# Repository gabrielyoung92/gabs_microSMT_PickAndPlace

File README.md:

# MicroSMT PNPv3 machine and feeders

Code, CAD, board files and operating notes for this machine. The hardware designs
and original firmware are by [MicroSMT](https://github.com/microsmt).
[Credits](CREDITS.md) · [Licences](THIRD_PARTY_NOTICES.md).

## Machine software

The Dell OptiPlex runs Debian 13 and OpenPnP. OpenPnP connects directly to the
Smoothieboard and cameras, and handles motion, pickup teaching, nozzles and jobs.
The feeder host owns the separate USB–RS485 adapter and serves the dashboard at
`http://machine-hostname/`, plain HTTP port 80 without login. OpenPnP advances
feeders through TCP `127.0.0.1:5001`.

| Software | Source and instructions |
| --- | --- |
| Dashboard, feeder host and OpenPnP companion | [USB_host/](Bing-feeder/V485-feeder/USB_host/README.md) |
| Universal feeder firmware **0.1.4**, bootloader and serial tools | [CODE_feeder/](Bing-feeder/V485-feeder/CODE_feeder/README.md) |
| Machine configuration and calibration | [Machine notes](Microsmt-PNPv3/docs/README.md) |
| EEPROM layout, saved settings and text/quantity limits | [EEPROM.md](EEPROM.md) |
| Remaining work | [TODO.md](TODO.md) |

The dashboard covers feeder state/errors, reel stock, motor/switch settings,
input tests and firmware updates. It also edits OpenPnP parts/packages and checks
remaining job stock. Tip compatibility is selected through packages; physical
nozzle setup stays in OpenPnP.

Build the feeder application with `pio run -e v485` from `CODE_feeder`.
It creates the dashboard firmware bundle automatically. Deploy the bundle and
select **Update** or **Update all outdated**, using the installed bootloader.
See the guides above for installation and operating details.

## Parts and boards

<p>

</p>

| Collection | Contents |
| --- | --- |
| [V485 feeders](Bing-feeder/V485-feeder/README.md) | 8/12/16/24 mm parts, PCBs and firmware |
| [V485 controller](Bing-feeder/V485-Feeder%20Controller/README.md) | ESP32-C3 controller and RS485 busbars |
| [V3 feeders](Bing-feeder/V3-feeder/README.md) | Parts, PCBs, source and assembly references |
| [V3 controller](Bing-feeder/V3-Feeder%20Controller/README.md) | Mega2560 sketch, controller PCB and busbars |
| [PNPv3 machine](Microsmt-PNPv3/README.md) | Frame parts, nozzle rack, strip feeders, motherboard and manuals |
| [KiCad projects](tools/kicad/README.md) | Editable board references, source comparisons and rebuild tools |
| [Missing V485 parts](V485-MISSING-PARTS.md) | Missing files and questions for the vendor |
| [STM32 source builds](Bing-feeder/STM32-BUILD.txt) | V485 build and V3 project requirements |

STL files are for printing; STEP files are for editing. Board folders contain
Gerbers, `KiCad/`, `docs/` and `photos/`. Keep each KiCad folder together for its
local libraries. Read the [recovery notes](tools/kicad/RECOVERY_NOTES.md) before
changing recovered copper or ordering boards.

View galleries on GitHub or with **Ctrl+Shift+V** in VS Code. Keep the photos
beside their READMEs. Machine profiles, stock databases, credentials and generated
builds remain outside Git. Local changes were prepared with ChatGPT assistance;
upstream attribution and licence notices remain in the repository.

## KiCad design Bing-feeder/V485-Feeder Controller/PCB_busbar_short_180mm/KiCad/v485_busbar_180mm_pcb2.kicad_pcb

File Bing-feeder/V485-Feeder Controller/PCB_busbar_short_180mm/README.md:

# V485 busbars — 180 mm

> Designs and original files by [MicroSMT](https://github.com/microsmt/Bing-feeder). [Credits and local changes](../../../CREDITS.md).

[Back to collection](../README.md)

Gerbers, editable KiCad files and previews are below.

## KiCad files

Open `.kicad_pro` in **KiCad 10**. Keep the whole `KiCad/` folder together; it contains the local libraries.

The schematics show pad numbers and connections. Use the supplied schematic for pin functions. Review the reported ERC/DRC findings before making a board.

| Project | Open in KiCad | Supporting reports |
| --- | --- | --- |
| V485 short busbar PCB1 | [v485_busbar_180mm_pcb1.kicad_pro](KiCad/v485_busbar_180mm_pcb1.kicad_pro) | [Recovery](docs/v485_busbar_180mm_pcb1-recovery.json) · [Validation](docs/v485_busbar_180mm_pcb1-validation.json) |
| V485 short busbar PCB2 | [v485_busbar_180mm_pcb2.kicad_pro](KiCad/v485_busbar_180mm_pcb2.kicad_pro) | [Recovery](docs/v485_busbar_180mm_pcb2-recovery.json) · [Validation](docs/v485_busbar_180mm_pcb2-validation.json) |
| V485 short busbar PCB4 | [v485_busbar_180mm_pcb4.kicad_pro](KiCad/v485_busbar_180mm_pcb4.kicad_pro) | [Recovery](docs/v485_busbar_180mm_pcb4-recovery.json) · [Validation](docs/v485_busbar_180mm_pcb4-validation.json) |

[Recovery details](docs/KICAD_RECOVERY.md) · [Method and editing limits](../../../tools/kicad/RECOVERY_NOTES.md)

## PCB1 Gerber views

[Download Gerber ZIP](Gerber_PCB1_2026-10-09.zip)

<table>
<tr>
<td align="center"><br><sub>Top</sub></td>
<td align="center"><br><sub>Bottom</sub></td>
<td align="center"><br><sub>Top-side isometric</sub></td>
</tr>
</table>

## PCB2 Gerber views

[Download Gerber ZIP](Gerber_PCB2_2026-10-09.zip)

<table>
<tr>
<td align="center"><br><sub>Top</sub></td>
<td align="center"><br><sub>Bottom</sub></td>
<td align="center"><br><sub>Top-side isometric</sub></td>
</tr>
</table>

## PCB4 Gerber views

[Download Gerber ZIP](Gerber_PCB4_2026-10-09.zip)

<table>
<tr>
<td align="center"><br><sub>Top</sub></td>
<td align="center"><br><sub>Bottom</sub></td>
<td align="center"><br><sub>Top-side isometric</sub></td>
</tr>
</table>

## Assembly notes

MicroSMT supplies 180 mm PCB busbars because the shorter sections are easier to transport. **PCB1, PCB2 and PCB4 each require two pieces.**

Gerber previews use display colours and an assumed 1.6 mm thickness; use source data for manufacturing dimensions.

## KiCad previews

KiCad reconstruction views; source Gerber views are above.

### V485 short busbar PCB1

<table>
<tr>
<td align="center"><br><sub>Recovered schematic</sub></td>
<td align="center"><br><sub>Recovered PCB top</sub></td>
<td align="center"><br><sub>Recovered PCB bottom</sub></td>
</tr>
</table>

[Sheet overview](photos/kicad-v485_busbar_180mm_pcb1-overview.jpg) · [Components 1](photos/kicad-v485_busbar_180mm_pcb1-sheet-01.jpg)

### V485 short busbar PCB2

<table>
<tr>
<td align="center"><br><sub>Recovered schematic</sub></td>
<td align="center"><br><sub>Recovered PCB top</sub></td>
<td align="center"><br><sub>Recovered PCB bottom</sub></td>
</tr>
</table>

[Sheet overview](photos/kicad-v485_busbar_180mm_pcb2-overview.jpg) · [Components 1](photos/kicad-v485_busbar_180mm_pcb2-sheet-01.jpg)

### V485 short busbar PCB4

<table>
<tr>
<td align="center"><br><sub>Recovered schematic</sub></td>
<td align="center"><br><sub>Recovered PCB top</sub></td>
<td align="center"><br><sub>Recovered PCB bottom</sub></td>
</tr>
</table>

[Sheet overview](photos/kicad-v485_busbar_180mm_pcb4-overview.jpg) · [Components 1](photos/kicad-v485_busbar_180mm_pcb4-sheet-01.jpg)

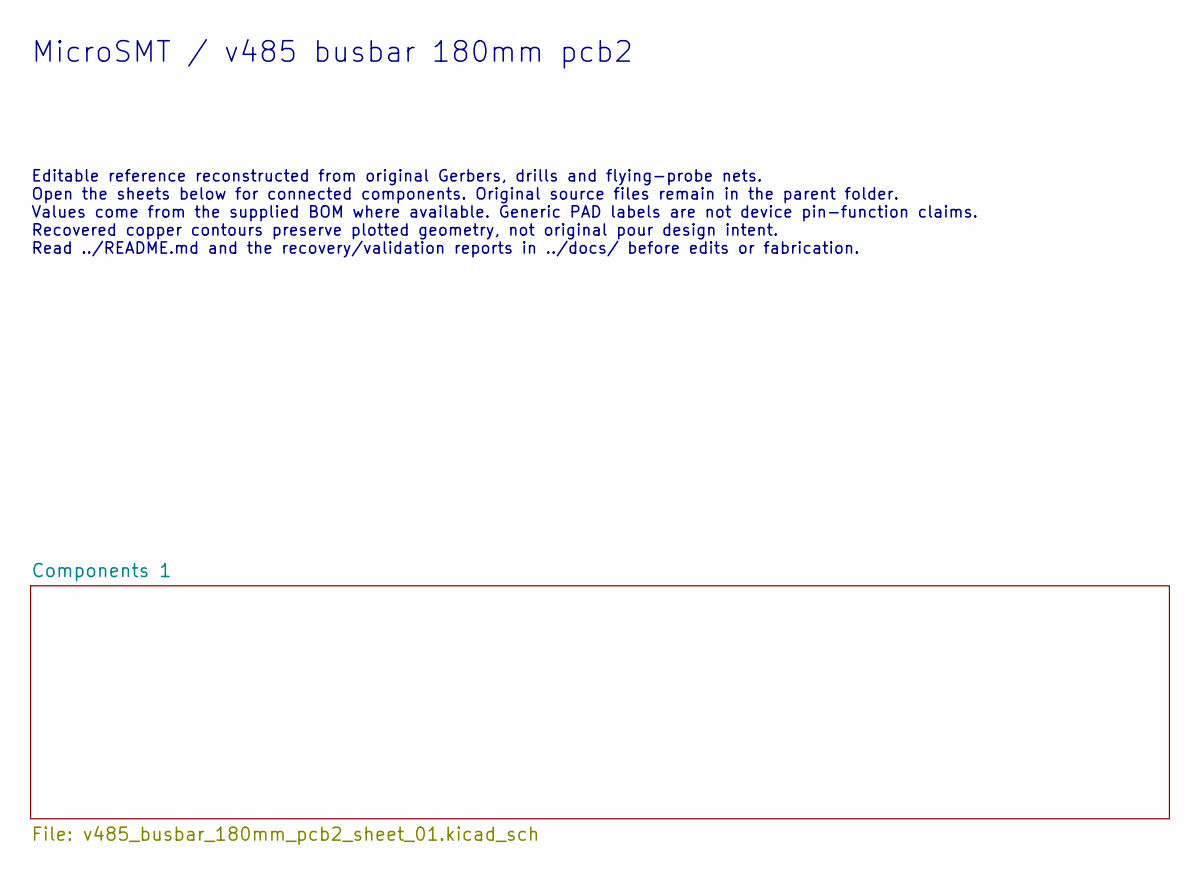
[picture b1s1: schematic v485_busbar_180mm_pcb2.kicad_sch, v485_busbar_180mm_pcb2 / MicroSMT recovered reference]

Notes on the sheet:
MicroSMT / v485 busbar 180mm pcb2
Editable reference reconstructed from original Gerbers, drills and flying-probe nets. Open the sheets below for connected components. Original source files remain in the parent folder. Values come from the supplied BOM where available. Generic PAD labels are not device pin-function claims. Recovere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

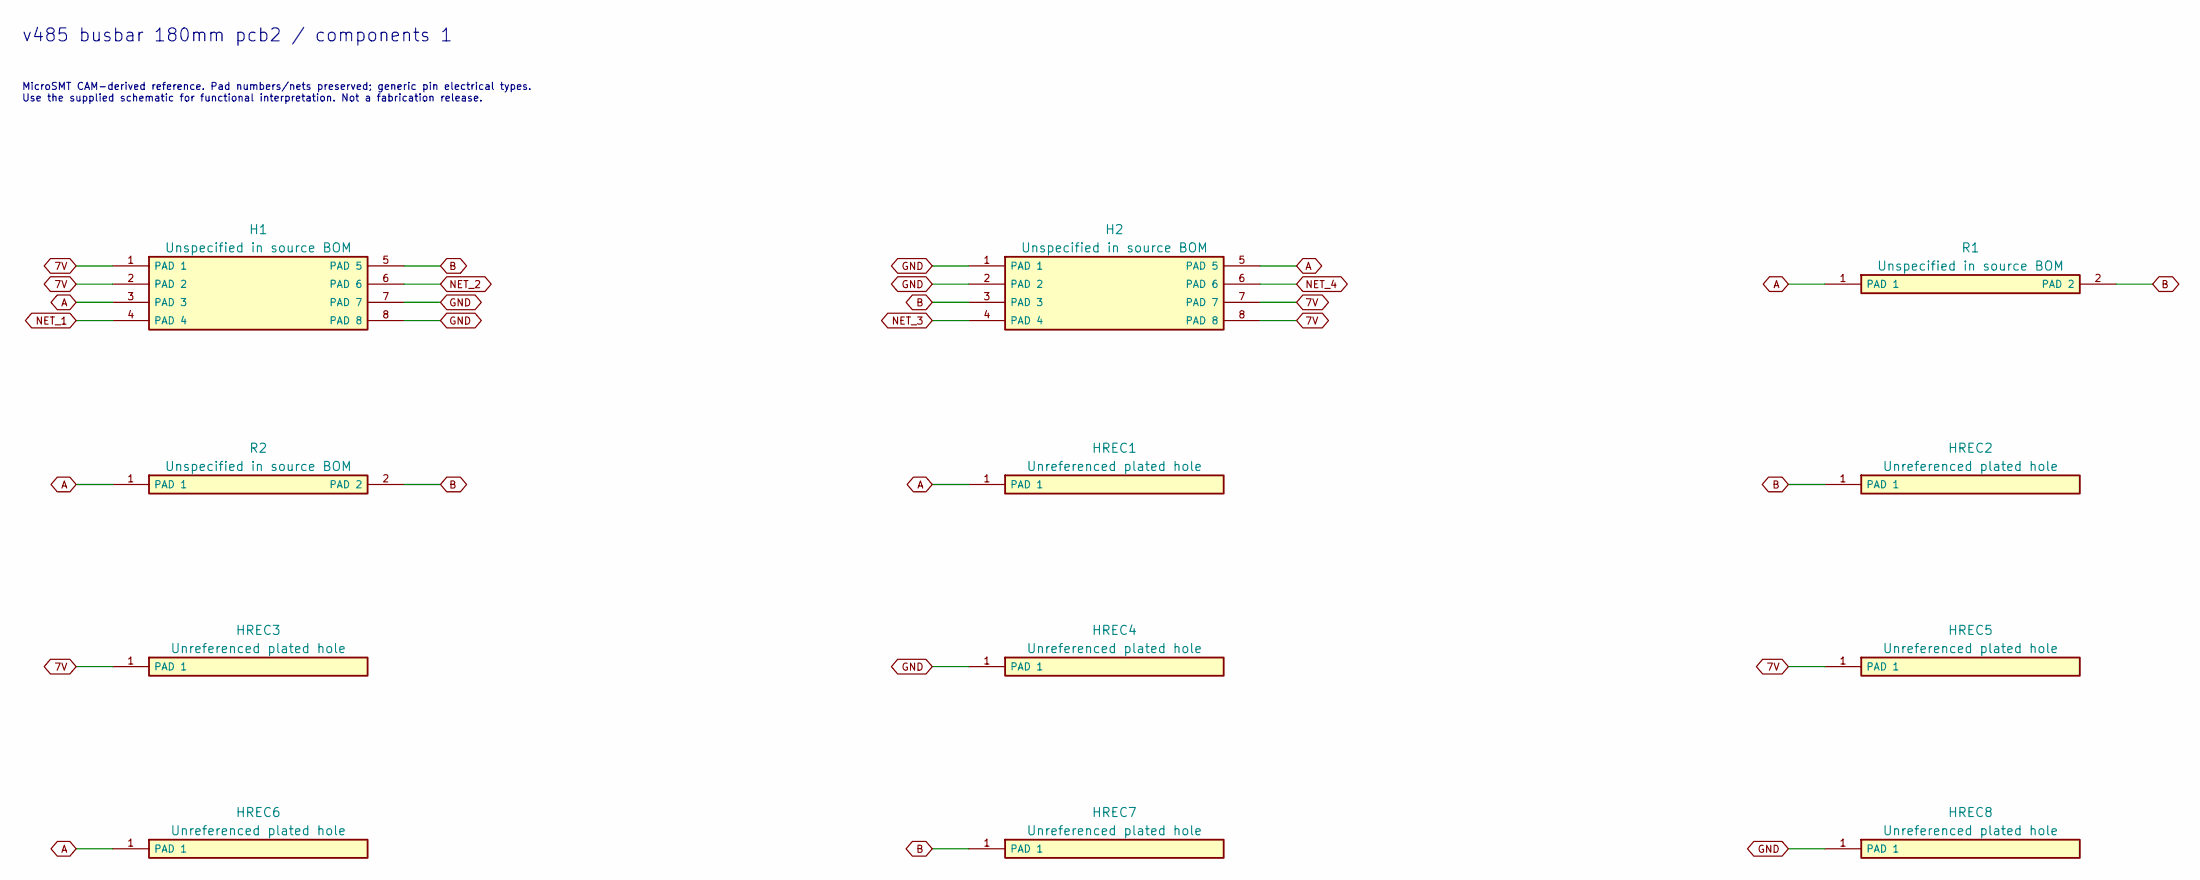
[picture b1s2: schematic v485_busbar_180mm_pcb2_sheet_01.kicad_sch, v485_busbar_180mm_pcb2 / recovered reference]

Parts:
H1: Unspecified in source BOM; SMD_8_72fee1c658
H2: Unspecified in source BOM; SMD_8_af5a7f26e5
HREC1, HREC2, HREC3, HREC4, HREC5, HREC6, HREC7, HREC8: Unreferenced plated hole; PTH_1_d32e30a0ea
R1, R2: Unspecified in source BOM; SMD_2_a7994fb989

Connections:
7V: H1.1 (PAD 1), H1.2 (PAD 2), H2.7 (PAD 7), H2.8 (PAD 8), HREC3.1, HREC5.1
A: H1.3 (PAD 3), H2.5 (PAD 5), HREC1.1, HREC6.1, R1.1 (PAD 1), R2.1 (PAD 1)
B: H1.5 (PAD 5), H2.3 (PAD 3), HREC2.1, HREC7.1, R1.2 (PAD 2), R2.2 (PAD 2)
GND: H1.7 (PAD 7), H1.8 (PAD 8), H2.1 (PAD 1), H2.2 (PAD 2), HREC4.1, HREC8.1
NET_1: H1.4 (PAD 4)
NET_2: H1.6 (PAD 6)
NET_3: H2.4 (PAD 4)
NET_4: H2.6 (PAD 6)

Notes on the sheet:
v485 busbar 180mm pcb2 / components 1
MicroSMT CAM-derived reference. Pad numbers/nets preserved; generic pin electrical types. Use the supplied schematic for functional interpretation. Not a fabrication release.

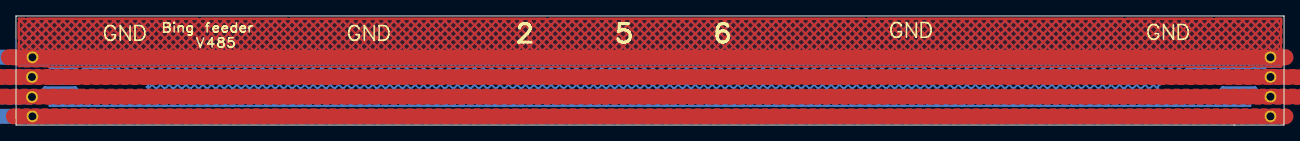
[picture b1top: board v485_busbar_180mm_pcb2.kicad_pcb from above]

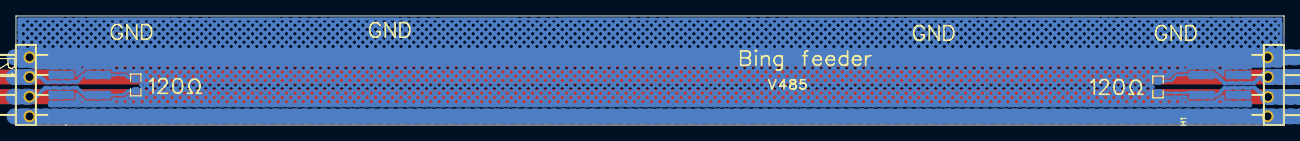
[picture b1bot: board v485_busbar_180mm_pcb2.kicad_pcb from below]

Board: 2 copper layers, 161.0 x 13.9 mm, 12 parts (4 on the bottom side), 4 nets.

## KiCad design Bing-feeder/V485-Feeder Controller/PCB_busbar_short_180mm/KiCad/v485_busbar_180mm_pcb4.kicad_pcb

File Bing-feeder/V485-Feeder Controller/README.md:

# V485 feeder controller

> Designs and original files by [MicroSMT](https://github.com/microsmt/Bing-feeder). [Credits and local changes](../../CREDITS.md).

This is the ESP32-C3 controller for the V485 feeder bus. The local firmware waits for an advance to finish before acknowledging M600, and also passes firmware updates from USB to the feeders over RS485. This machine uses the [direct USB–RS485 PC host](../V485-feeder/USB_host/README.md); the ESP32 controller is an alternative bus bridge.

| Browse | Contents |
| --- | --- |
| [Controller PCB](PCB_ControlBoard/README.md) | Gerber ZIP, schematic, BOM and three board views |
| [ESP32-C3 firmware](CODE_esp32C3/README.md) | PlatformIO C++ project, configuration and module notes |
| [180 mm busbars](PCB_busbar_short_180mm/README.md) | Three Gerber sets with individual board previews |
| [480 mm busbar](PCB_busbar_long_480mm/README.md) | Gerber ZIP, supplied notes and three board views |

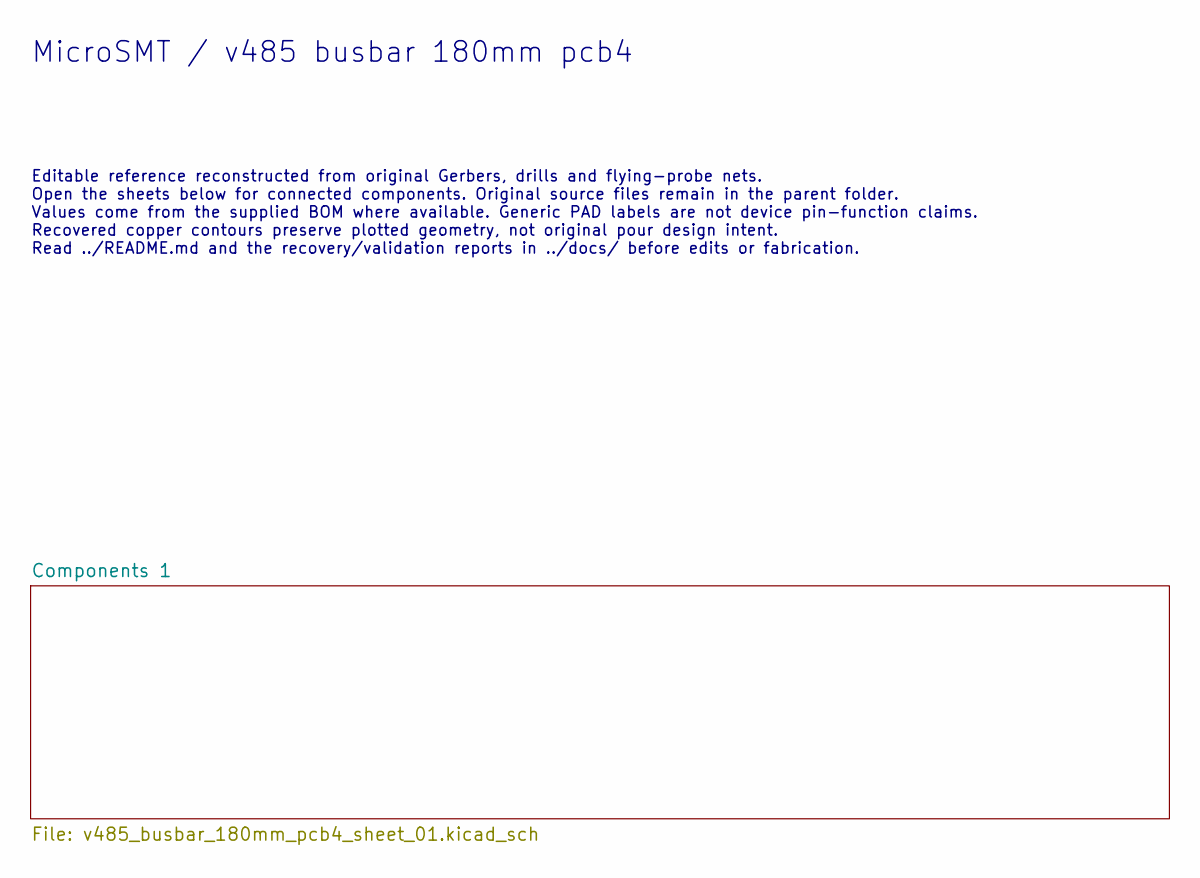
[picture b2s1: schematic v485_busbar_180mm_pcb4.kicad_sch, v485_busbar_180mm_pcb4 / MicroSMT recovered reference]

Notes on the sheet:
MicroSMT / v485 busbar 180mm pcb4
Editable reference reconstructed from original Gerbers, drills and flying-probe nets. Open the sheets below for connected components. Original source files remain in the parent folder. Values come from the supplied BOM where available. Generic PAD labels are not device pin-function claims. Recovere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

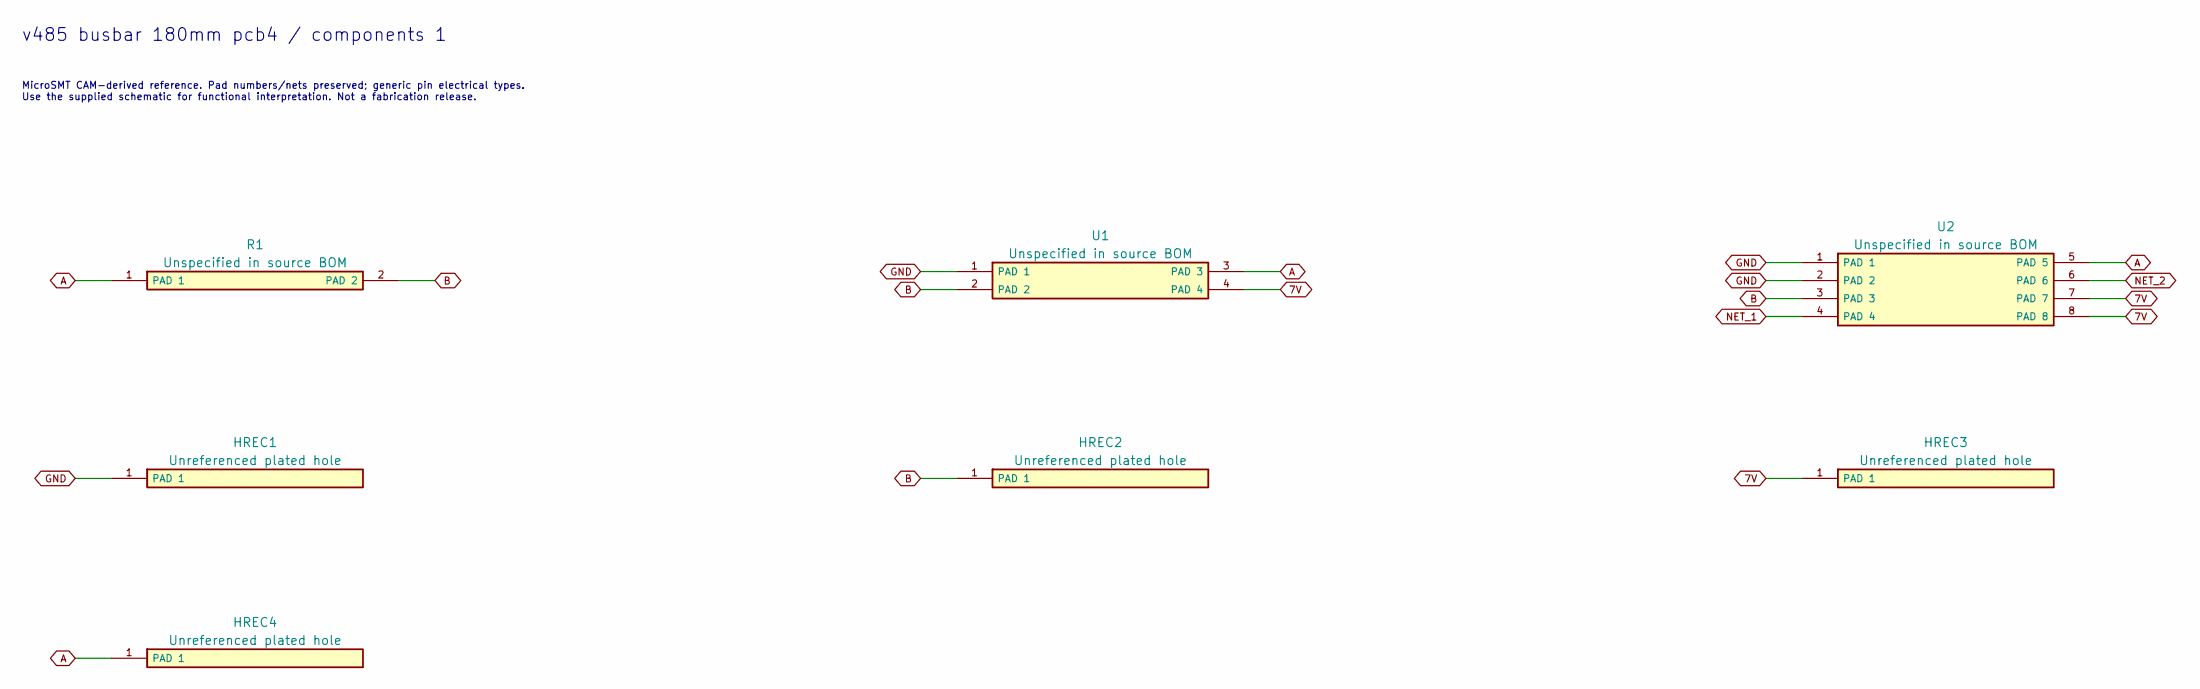
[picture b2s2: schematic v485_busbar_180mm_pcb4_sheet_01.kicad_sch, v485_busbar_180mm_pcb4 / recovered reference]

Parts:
HREC1, HREC2, HREC3, HREC4: Unreferenced plated hole; PTH_1_d32e30a0ea
R1: Unspecified in source BOM; SMD_2_fef7677169
U1: Unspecified in source BOM; PTH_4_2a8f111d21
U2: Unspecified in source BOM; SMD_8_2b0fda5f30

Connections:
7V: HREC3.1, U1.4 (PAD 4), U2.7 (PAD 7), U2.8 (PAD 8)
A: HREC4.1, R1.1 (PAD 1), U1.3 (PAD 3), U2.5 (PAD 5)
B: HREC2.1, R1.2 (PAD 2), U1.2 (PAD 2), U2.3 (PAD 3)
GND: HREC1.1, U1.1 (PAD 1), U2.1 (PAD 1), U2.2 (PAD 2)
NET_1: U2.4 (PAD 4)
NET_2: U2.6 (PAD 6)

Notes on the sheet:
v485 busbar 180mm pcb4 / components 1
MicroSMT CAM-derived reference. Pad numbers/nets preserved; generic pin electrical types. Use the supplied schematic for functional interpretation. Not a fabrication release.

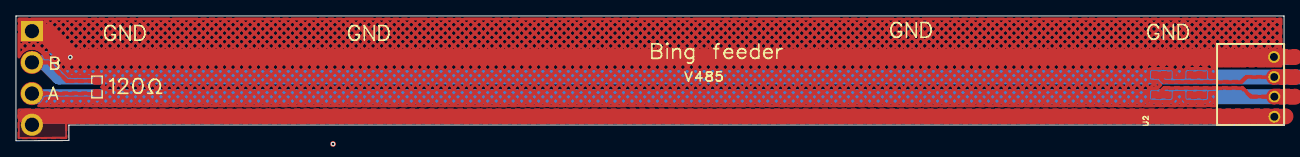
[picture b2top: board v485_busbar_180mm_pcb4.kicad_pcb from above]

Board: 2 copper layers, 161.0 x 15.8 mm, 7 parts (1 on the bottom side), 4 nets.

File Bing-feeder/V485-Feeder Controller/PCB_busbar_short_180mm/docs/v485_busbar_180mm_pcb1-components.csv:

Reference,Value,Recovered footprint,Pad count,Inferred reference
R1,Unspecified in source BOM,MicroSMT_v485_busbar_180mm_pcb1:SMD_2_fef7677169,2,False
U1,Unspecified in source BOM,MicroSMT_v485_busbar_180mm_pcb1:PTH_4_06e8961db4,4,False
U2,Unspecified in source BOM,MicroSMT_v485_busbar_180mm_pcb1:SMD_8_a8244cd5c0,8,False
HREC1,Unreferenced plated hole,MicroSMT_v485_busbar_180mm_pcb1:PTH_1_d32e30a0ea,1,True
HREC2,Unreferenced plated hole,MicroSMT_v485_busbar_180mm_pcb1:PTH_1_d32e30a0ea,1,True
HREC3,Unreferenced plated hole,MicroSMT_v485_busbar_180mm_pcb1:PTH_1_d32e30a0ea,1,True
HREC4,Unreferenced plated hole,MicroSMT_v485_busbar_180mm_pcb1:PTH_1_d32e30a0ea,1,True

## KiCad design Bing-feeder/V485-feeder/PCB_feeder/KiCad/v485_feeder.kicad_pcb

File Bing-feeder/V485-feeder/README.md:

# V485 feeder

> Designs and original files by [MicroSMT](https://github.com/microsmt/Bing-feeder). [Credits and local changes](../../CREDITS.md).

Choose your feeder width below. These folders include the wider V485 parts added in the 21 October 2026 download, along with the boards and local firmware.

| Browse | Contents |
| --- | --- |
| [8 mm parts](3D_parts_8mm/README.md) | 23 parts with STEP/STL links and nine previews per part |
| [12 mm parts](3D_parts_12mm/README.md) | 11 parts with STEP/STL links and nine previews per part |
| [16 mm parts](3D_parts_16mm/README.md) | 10 parts with STEP/STL links and nine previews per part |
| [24 mm parts](3D_parts_24mm/README.md) | 10 parts with STEP/STL links and nine previews per part |
| [Shared wider-feeder parts](3D_parts_shared/README.md) | 5 parts with STEP/STL links and nine previews per part |
| [Feeder PCB](PCB_feeder/README.md) | Gerber ZIP, schematic, BOM and three board views |
| [Display PCB](PCB_display/README.md) | Gerber ZIP, schematic, BOM and three board views |
| [USB host service](USB_host/README.md) | Port 80 dashboard, direct USB–RS485, feeder TCP, stock/configuration and firmware queue |
| [Feeder firmware](CODE_feeder/README.md) | Version 0.1.4: universal application, switch-controlled peel completion and motor-off input tests |

Shared wider-feeder parts are in [their own folder](3D_parts_shared/README.md).
See [missing parts](../../V485-MISSING-PARTS.md) and the
[source comparison](../UPSTREAM-2026-10-25.md) for file coverage.

## Software on this machine

The [PC host](USB_host/README.md) manages the powered feeders. OpenPnP owns the
Smoothieboard serial connection, cameras, pickup locations, physical nozzle setup
and jobs. The host exposes feeder TCP on `127.0.0.1:5001` and a compact web page
on port 80. Normal firmware updates use the installed bootloader; one universal
application covers 8/12/16/24 mm units.

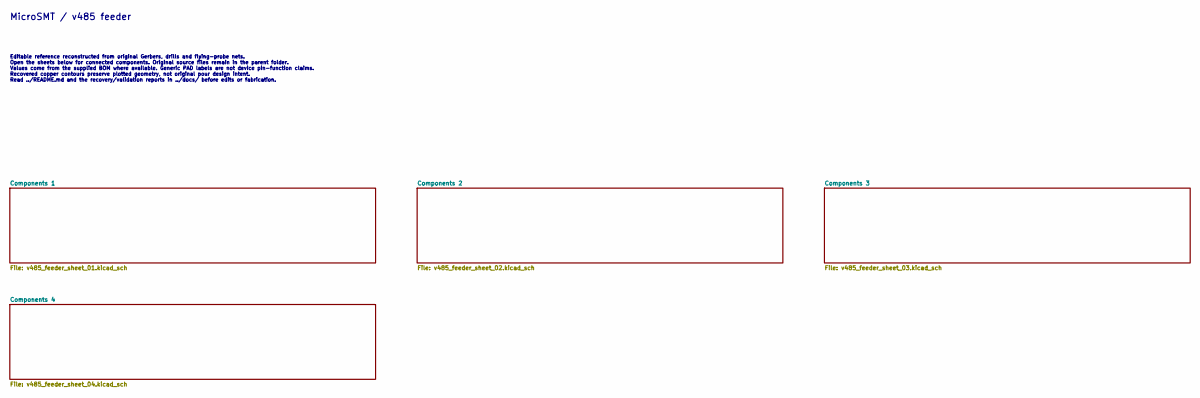
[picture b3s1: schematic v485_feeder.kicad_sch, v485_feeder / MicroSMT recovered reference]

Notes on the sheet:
MicroSMT / v485 feeder
Editable reference reconstructed from original Gerbers, drills and flying-probe nets. Open the sheets below for connected components. Original source files remain in the parent folder. Values come from the supplied BOM where available. Generic PAD labels are not device pin-function claims. Recovere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

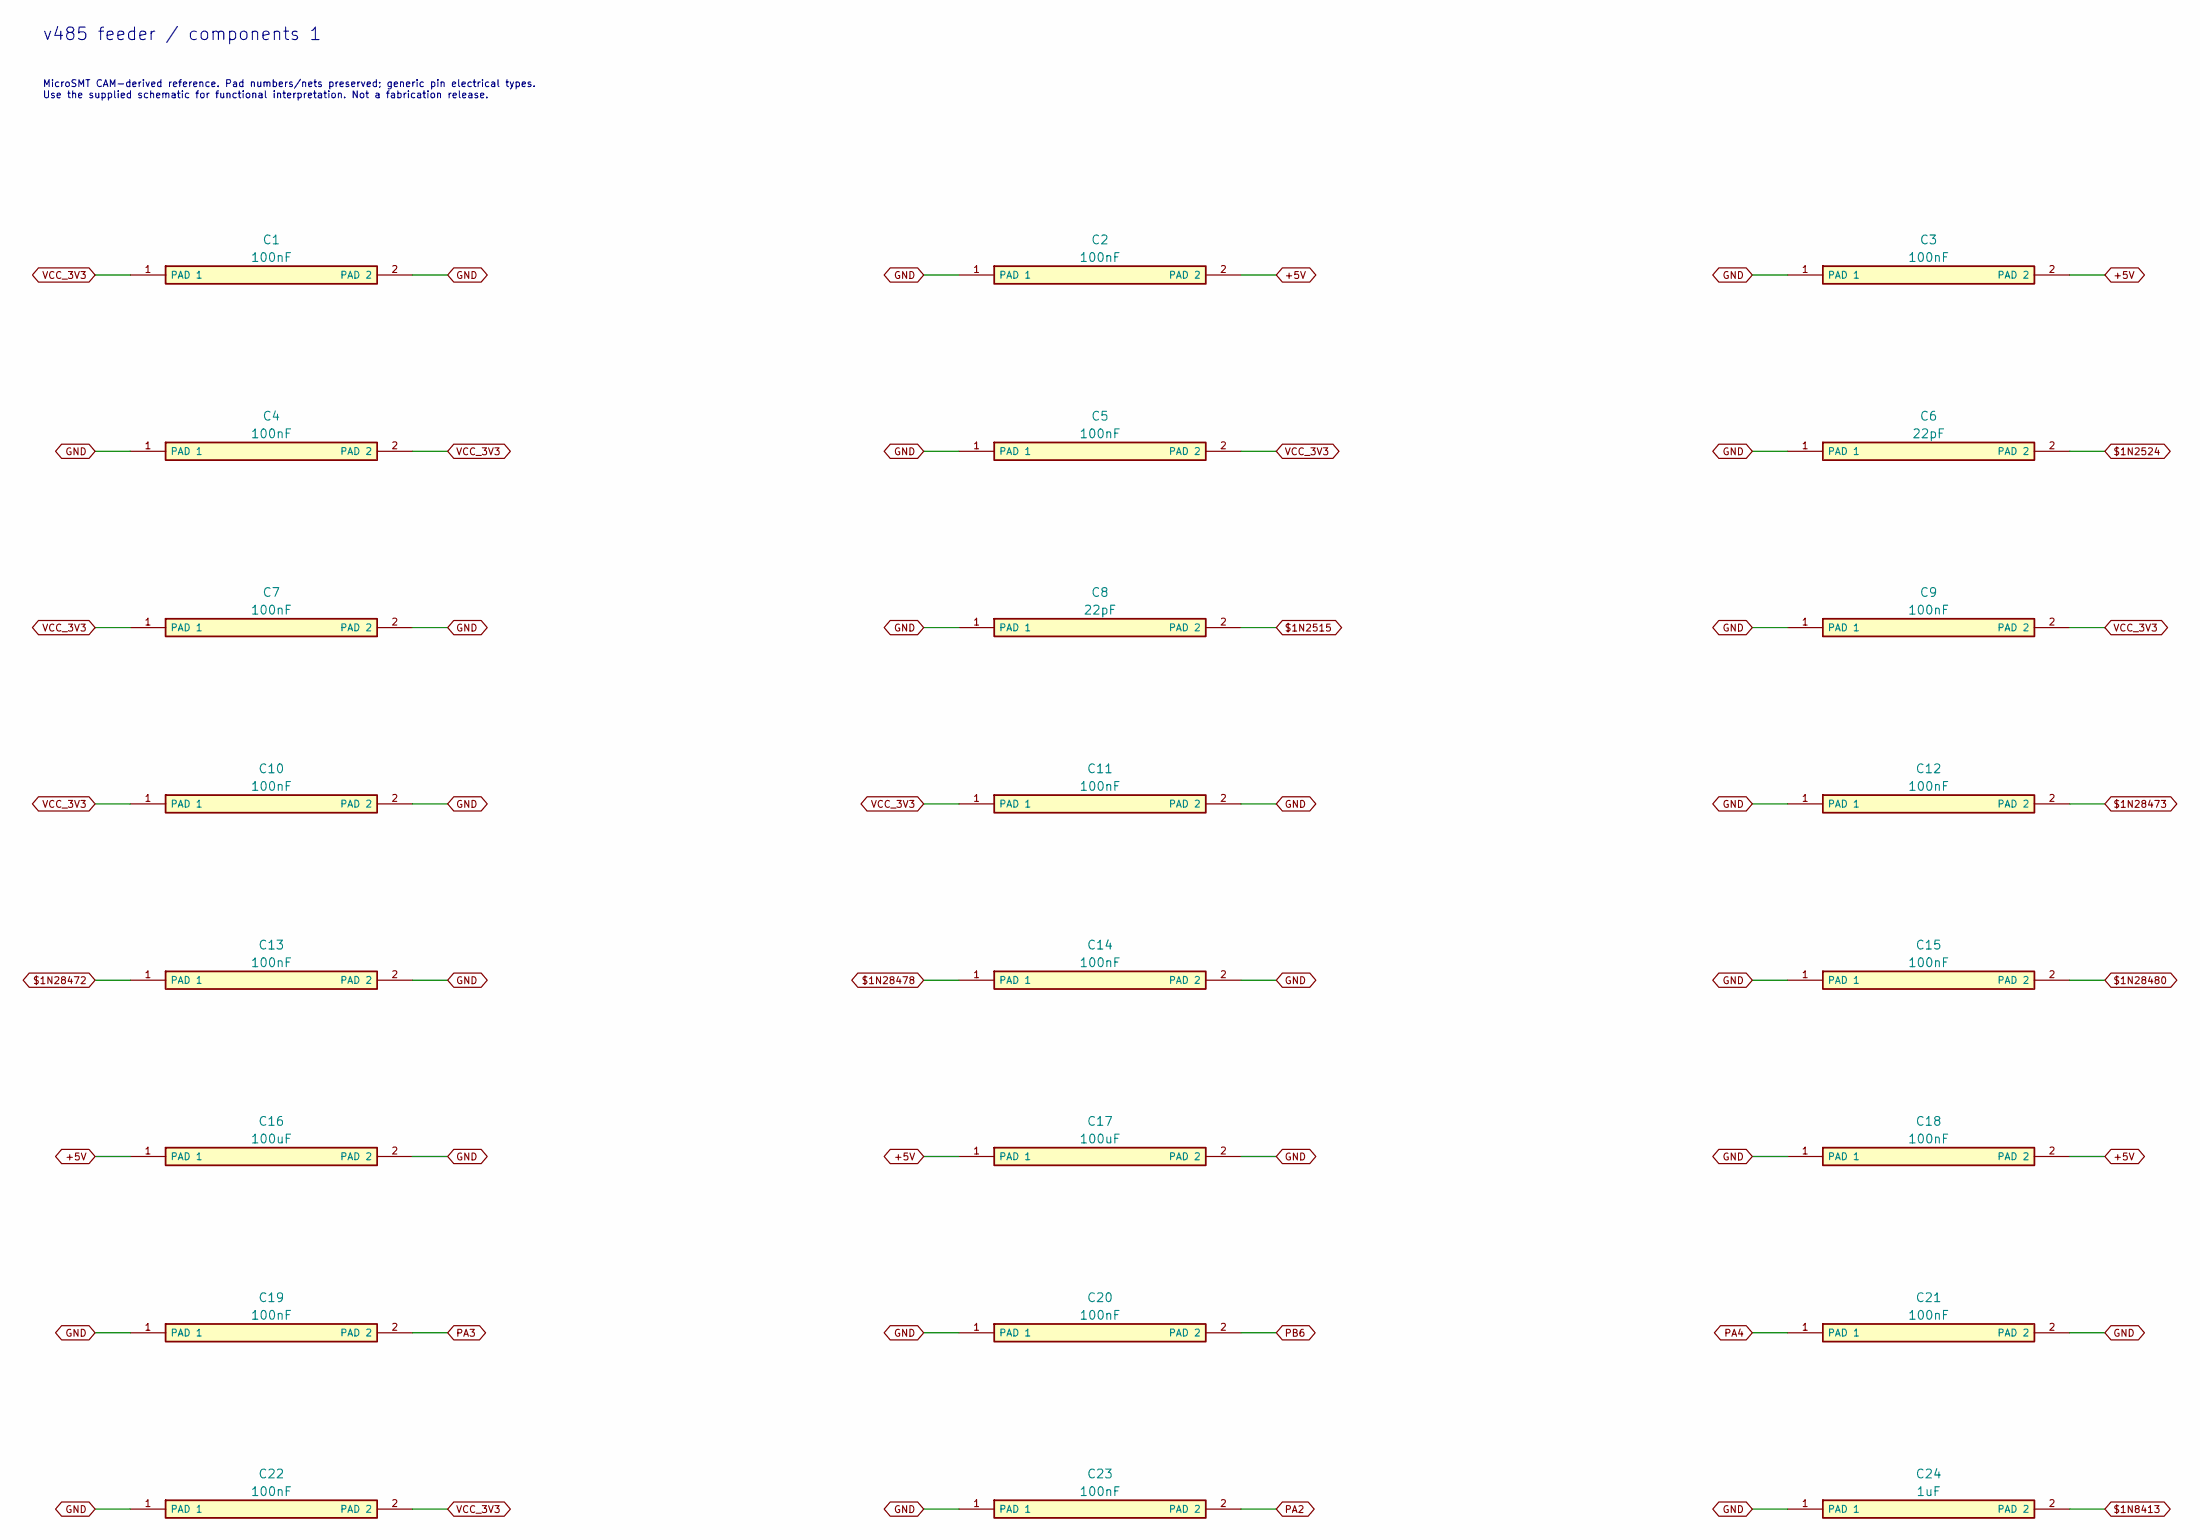
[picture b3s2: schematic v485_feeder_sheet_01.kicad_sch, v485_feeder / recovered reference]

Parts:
C1, C9, C10: 100nF; SMD_2_c1a3413776
C2: 100nF; SMD_2_829407ff48
C3, C11: 100nF; SMD_2_44635c1159
C4, C5, C7, C19, C20, C22: 100nF; SMD_2_cf0339bc75
C6: 22pF; SMD_2_874df9096d
C8: 22pF; SMD_2_aac479f3ea
C12, C13: 100nF; SMD_2_4db5f12e3d
C14, C15, C18: 100nF; SMD_2_3dfdeb042f
C16, C17: 100uF; SMD_2_6e07a3e01f
C21: 100nF; SMD_2_874df9096d
C23: 100nF; SMD_2_aac479f3ea
C24: 1uF; SMD_2_874df9096d

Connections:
$1N2515: C8.2 (PAD 2); also elsewhere on the board
$1N2524: C6.2 (PAD 2); also elsewhere on the board
$1N8413: C24.2 (PAD 2); also elsewhere on the board
$1N28472: C13.1 (PAD 1); also elsewhere on the board
$1N28473: C12.2 (PAD 2); also elsewhere on the board
$1N28478: C14.1 (PAD 1); also elsewhere on the board
$1N28480: C15.2 (PAD 2); also elsewhere on the board
+5V: C2.2 (PAD 2), C3.2 (PAD 2), C16.1 (PAD 1), C17.1 (PAD 1), C18.2 (PAD 2); also elsewhere on the board
GND: C1.2 (PAD 2), C2.1 (PAD 1), C3.1 (PAD 1), C4.1 (PAD 1), C5.1 (PAD 1), C6.1 (PAD 1), C7.2 (PAD 2), C8.1 (PAD 1), C9.1 (PAD 1), C10.2 (PAD 2), C11.2 (PAD 2), C12.1 (PAD 1), C13.2 (PAD 2), C14.2 (PAD 2), C15.1 (PAD 1), C16.2 (PAD 2), C17.2 (PAD 2), C18.1 (PAD 1), C19.1 (PAD 1), C20.1 (PAD 1), C21.2 (PAD 2), C22.1 (PAD 1), C23.1 (PAD 1), C24.1 (PAD 1); also elsewhere on the board
PA2: C23.2 (PAD 2); also elsewhere on the board
PA3: C19.2 (PAD 2); also elsewhere on the board
PA4: C21.1 (PAD 1); also elsewhere on the board
PB6: C20.2 (PAD 2); also elsewhere on the board
VCC_3V3: C1.1 (PAD 1), C4.2 (PAD 2), C5.2 (PAD 2), C7.1 (PAD 1), C9.2 (PAD 2), C10.1 (PAD 1), C11.1 (PAD 1), C22.2 (PAD 2); also elsewhere on the board

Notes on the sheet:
v485 feeder / components 1
MicroSMT CAM-derived reference. Pad numbers/nets preserved; generic pin electrical types. Use the supplied schematic for functional interpretation. Not a fabrication release.

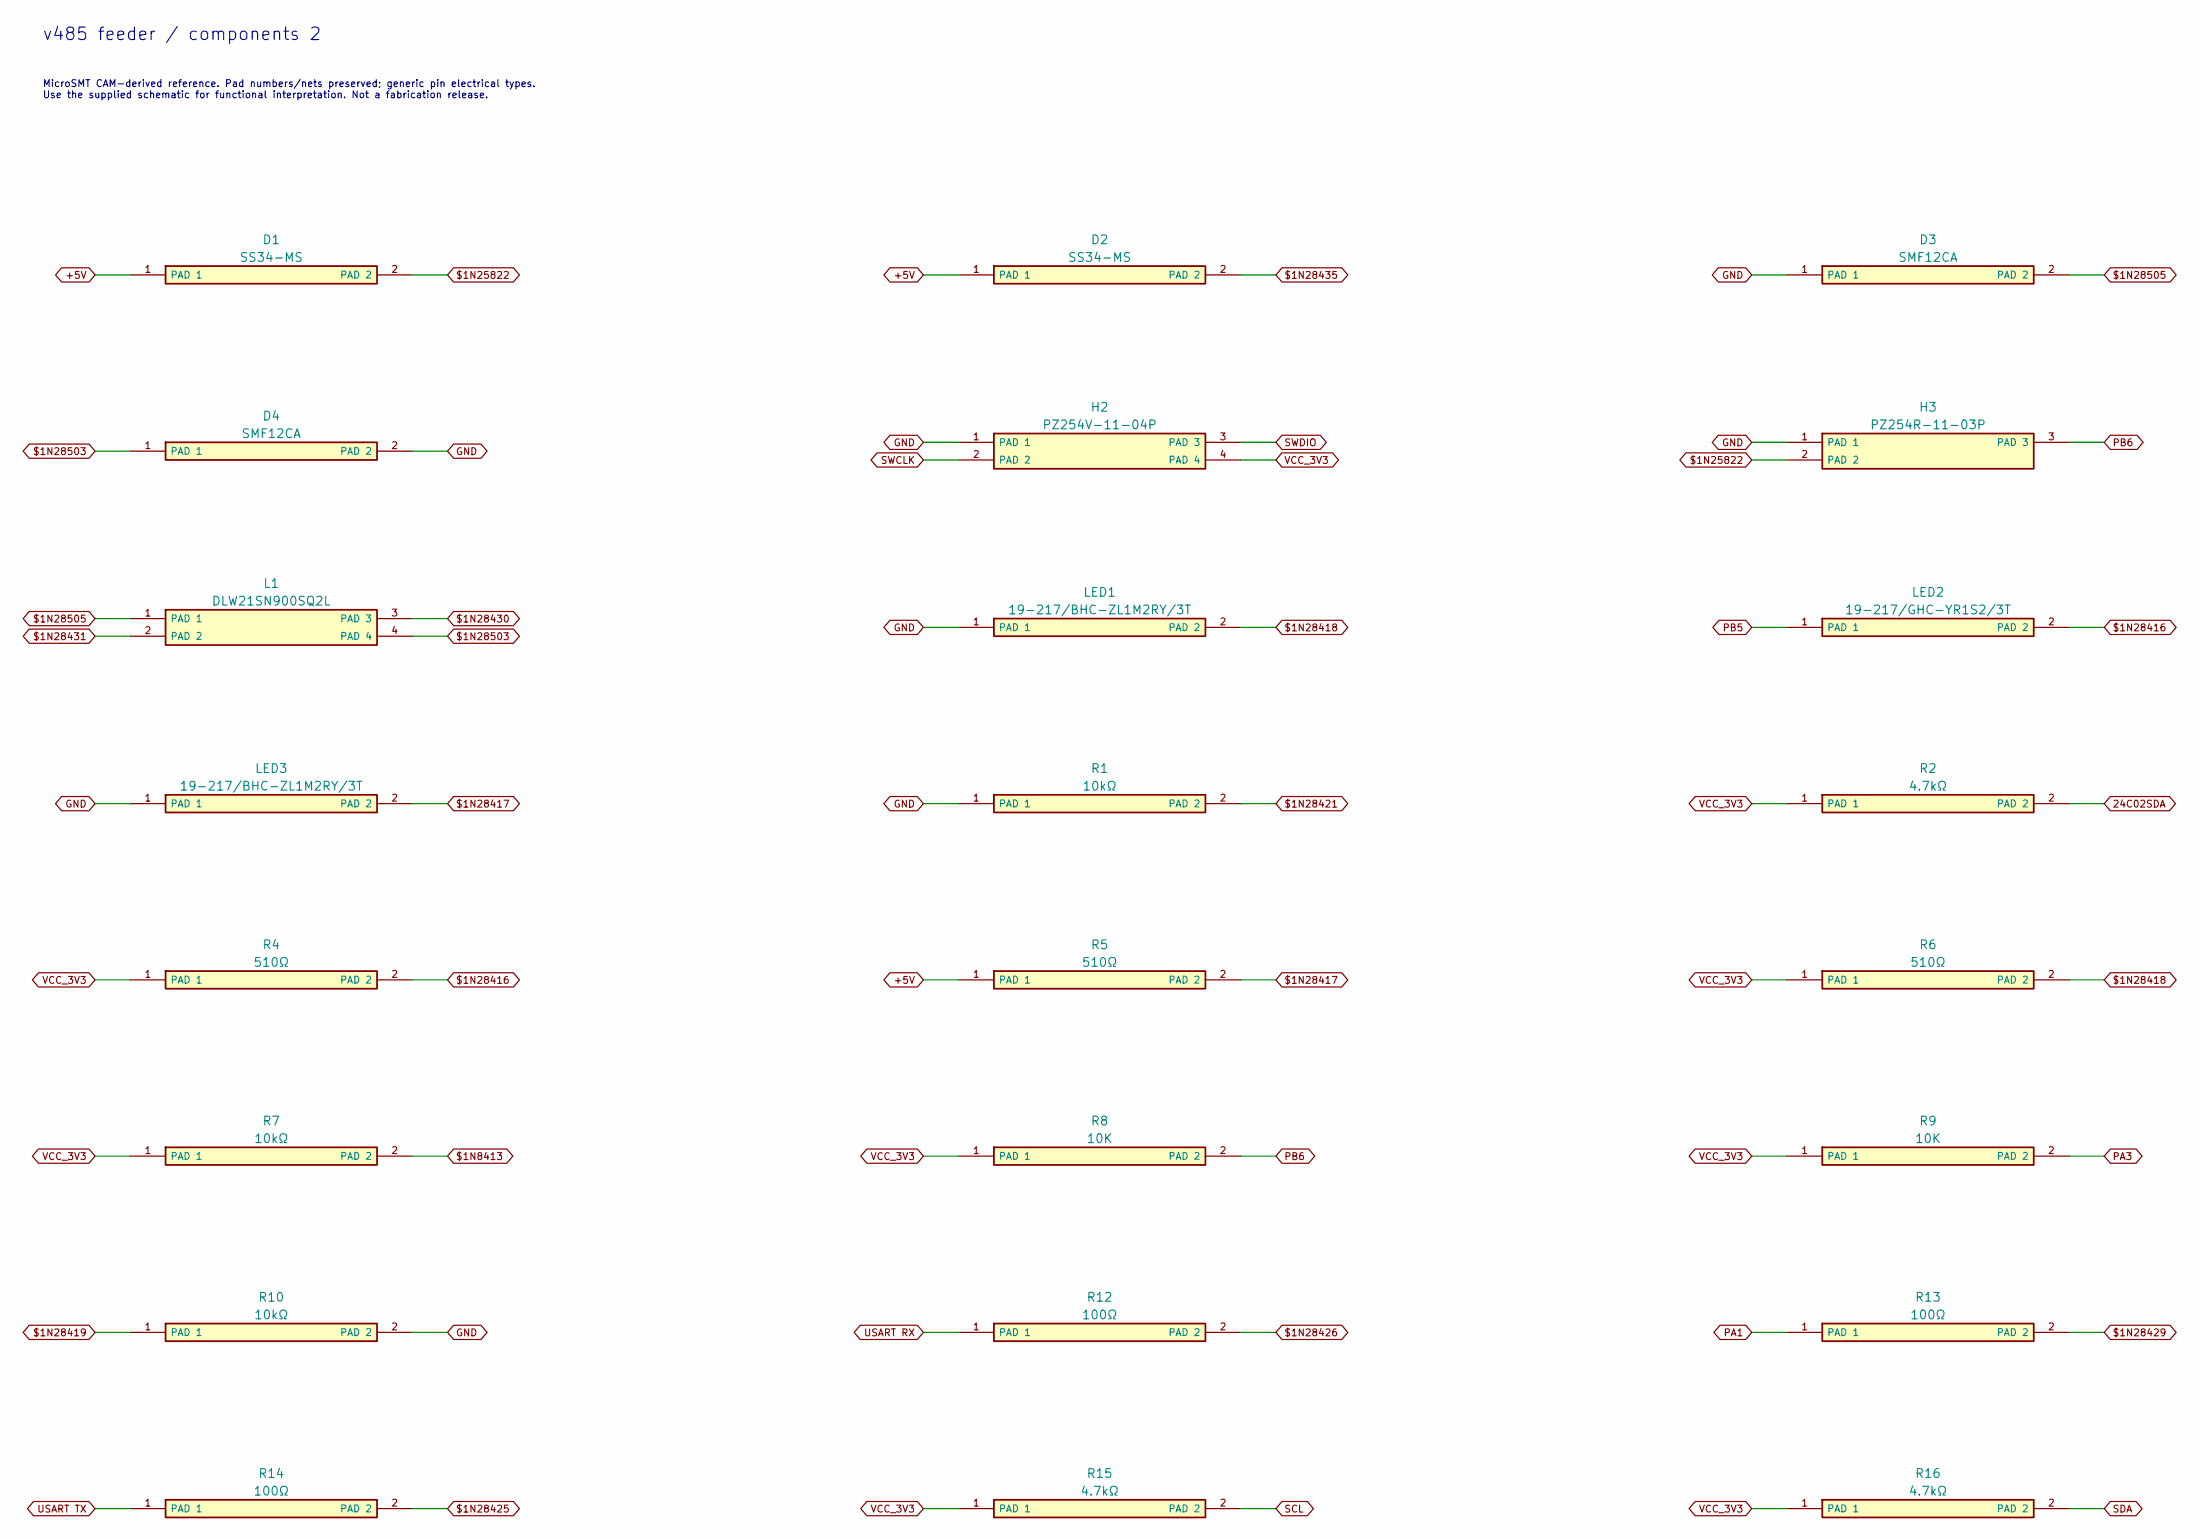
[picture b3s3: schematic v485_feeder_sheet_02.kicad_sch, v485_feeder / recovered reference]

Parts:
D1: SS34-MS; SMD_2_2eb83b068d
D2: SS34-MS; SMD_2_0e04a25b7f
D3, D4: SMF12CA; SMD_2_8d21fd2c67
H2: PZ254V-11-04P; PTH_4_3fe72de8b5
H3: PZ254R-11-03P; PTH_3_d1691705db
L1: DLW21SN900SQ2L; SMD_4_7982c82c77
LED1: 19-217/BHC-ZL1M2RY/3T; SMD_2_651440e7dc
LED2: 19-217/GHC-YR1S2/3T; SMD_2_262bb741d3
LED3: 19-217/BHC-ZL1M2RY/3T; SMD_2_eb93cb215b
R1, R10: 10kΩ; SMD_2_e7bda1677c
R2: 4.7kΩ; SMD_2_e7bda1677c
R4, R5: 510Ω; SMD_2_91fcdf277d
R6: 510Ω; SMD_2_e7bda1677c
R7: 10kΩ; SMD_2_91fcdf277d
R8: 10K; SMD_2_04577a26f8
R9: 10K; SMD_2_cc916b3528
R12, R13, R14: 100Ω; SMD_2_e7bda1677c
R15, R16: 4.7kΩ; SMD_2_bcd5a0224c

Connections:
24C02SDA: R2.2 (PAD 2); also elsewhere on the board
$1N8413: R7.2 (PAD 2); also elsewhere on the board
$1N25822: D1.2 (PAD 2), H3.2 (PAD 2)
$1N28416: LED2.2 (PAD 2), R4.2 (PAD 2)
$1N28417: LED3.2 (PAD 2), R5.2 (PAD 2)
$1N28418: LED1.2 (PAD 2), R6.2 (PAD 2)
$1N28419: R10.1 (PAD 1); also elsewhere on the board
$1N28421: R1.2 (PAD 2); also elsewhere on the board
$1N28425: R14.2 (PAD 2); also elsewhere on the board
$1N28426: R12.2 (PAD 2); also elsewhere on the board
$1N28429: R13.2 (PAD 2); also elsewhere on the board
$1N28430: L1.3 (PAD 3); also elsewhere on the board
$1N28431: L1.2 (PAD 2); also elsewhere on the board
$1N28435: D2.2 (PAD 2); also elsewhere on the board
$1N28503: D4.1 (PAD 1), L1.4 (PAD 4); also elsewhere on the board
$1N28505: D3.2 (PAD 2), L1.1 (PAD 1); also elsewhere on the board
+5V: D1.1 (PAD 1), D2.1 (PAD 1), R5.1 (PAD 1); also elsewhere on the board
GND: D3.1 (PAD 1), D4.2 (PAD 2), H2.1 (PAD 1), H3.1 (PAD 1), LED1.1 (PAD 1), LED3.1 (PAD 1), R1.1 (PAD 1), R10.2 (PAD 2); also elsewhere on the board
PA1: R13.1 (PAD 1); also elsewhere on the board
PA3: R9.2 (PAD 2); also elsewhere on the board
PB5: LED2.1 (PAD 1); also elsewhere on the board
PB6: H3.3 (PAD 3), R8.2 (PAD 2); also elsewhere on the board
SCL: R15.2 (PAD 2); also elsewhere on the board
SDA: R16.2 (PAD 2); also elsewhere on the board
SWCLK: H2.2 (PAD 2); also elsewhere on the board
SWDIO: H2.3 (PAD 3); also elsewhere on the board
USART RX: R12.1 (PAD 1); also elsewhere on the board
USART TX: R14.1 (PAD 1); also elsewhere on the board
VCC_3V3: H2.4 (PAD 4), R2.1 (PAD 1), R4.1 (PAD 1), R6.1 (PAD 1), R7.1 (PAD 1), R8.1 (PAD 1), R9.1 (PAD 1), R15.1 (PAD 1), R16.1 (PAD 1); also elsewhere on the board

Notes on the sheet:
v485 feeder / components 2
MicroSMT CAM-derived reference. Pad numbers/nets preserved; generic pin electrical types. Use the supplied schematic for functional interpretation. Not a fabrication release.
